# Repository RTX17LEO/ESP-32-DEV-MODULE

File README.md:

ESP32 Dev Board Project

The ESP32 Dev Module is a powerful microcontroller with built-in Wi-Fi and Bluetooth, widely used for IoT and embedded applications.  
This project includes the schematic and PCB design of an ESP32 Dev Module created using KiCad.  
The schematic defines connections for power, EN pin, and basic components like resistors and capacitors.  
A 2-layer PCB is designed with proper routing and clearance rules followed.  
KiCad is used for schematic capture, footprint assignment, and PCB layout, and Gerber files are generated for manufacturing.

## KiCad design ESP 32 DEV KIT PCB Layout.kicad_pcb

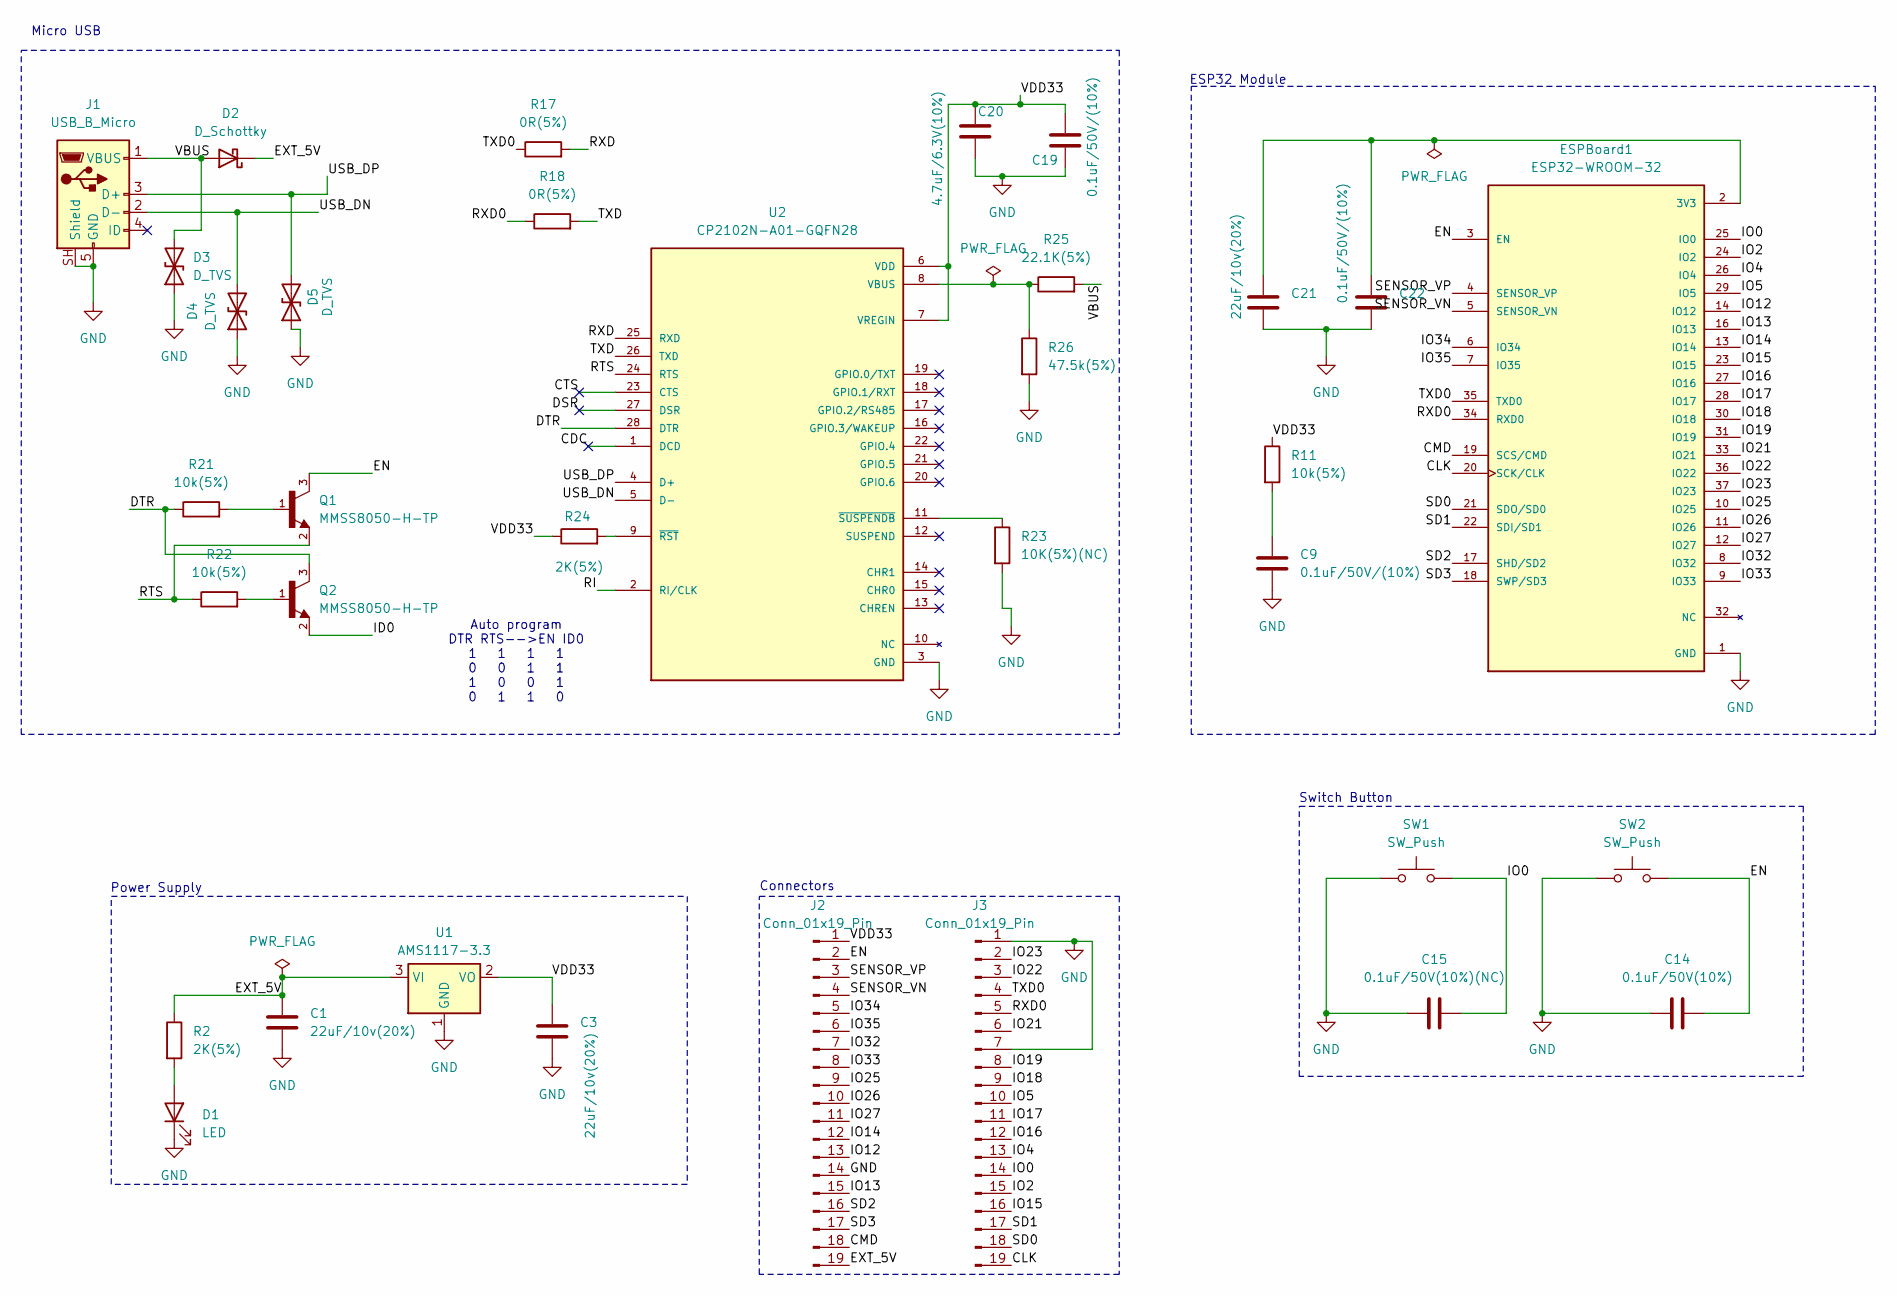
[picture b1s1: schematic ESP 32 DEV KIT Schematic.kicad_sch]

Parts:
C1, C3, C21: 22uF/10v(20%); C_0201_0603Metric
C9, C19, C22: 0.1uF/50V/(10%); C_01005_0402Metric
C14: 0.1uF/50V(10%); C_01005_0402Metric
C15: 0.1uF/50V(10%)(NC); C_01005_0402Metric
C20: 4.7uF/6.3V(10%); C_01005_0402Metric
D1: LED; LED_0603_1608Metric
D2: D_Schottky; D_SOD-323
D3, D4, D5: D_TVS; D_SOD-523
ESPBoard1: ESP32-WROOM-32; MODULE_ESP32-WROOM-32; PARTREV 2.9
J1: USB_B_Micro; USB_Micro-B_Molex_47346-0001
J2, J3: Conn_01x19_Pin; PinHeader_1x19_P2.54mm_Vertical
Q1, Q2: MMSS8050-H-TP; TRANS_MMSS8050-H-TP; PARTREV D
R2, R24: 2K(5%); R_01005_0402Metric
R11, R21, R22: 10k(5%); R_01005_0402Metric
R17, R18: 0R(5%); R_01005_0402Metric
R23: 10K(5%)(NC); R_01005_0402Metric
R25: 22.1K(5%); R_01005_0402Metric
R26: 47.5k(5%); R_01005_0402Metric
SW1, SW2: SW_Push; SW_SPST_B3S-1000
U1: AMS1117-3.3; SOT-223-3_TabPin2
U2: CP2102N-A01-GQFN28; QFN50P500X500X80-29N; PARTREV 1.0

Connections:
/CDC: U2.1 (DCD)
/CLK: ESPBoard1.20 (SCK/CLK), J3.19
/CMD: ESPBoard1.19 (SCS/CMD), J2.18
/CTS: U2.23 (CTS)
/DSR: U2.27 (DSR)
/DTR: Q2.3, R21.1, U2.28 (DTR)
/EN: C14.2, ESPBoard1.3 (EN), J2.2, Q1.3, SW2.2; also elsewhere on the board
/EXT_5V: C1.1, D2.1 (K), J2.19, R2.1, U1.3 (VI)
/ID0: Q2.2
/IO0: C15.2, ESPBoard1.25 (IO0), J3.14, SW1.2; also elsewhere on the board
/IO2: ESPBoard1.24 (IO2), J3.15
/IO4: ESPBoard1.26 (IO4), J3.13
/IO5: ESPBoard1.29 (IO5), J3.10
/IO12: ESPBoard1.14 (IO12), J2.13
/IO13: ESPBoard1.16 (IO13), J2.15
/IO14: ESPBoard1.13 (IO14), J2.12
/IO15: ESPBoard1.23 (IO15), J3.16
/IO16: ESPBoard1.27 (IO16), J3.12
/IO17: ESPBoard1.28 (IO17), J3.11
/IO18: ESPBoard1.30 (IO18), J3.9
/IO19: ESPBoard1.31 (IO19), J3.8
/IO21: ESPBoard1.33 (IO21), J3.6
/IO22: ESPBoard1.36 (IO22), J3.3
/IO23: ESPBoard1.37 (IO23), J3.2
/IO25: ESPBoard1.10 (IO25), J2.9
/IO26: ESPBoard1.11 (IO26), J2.10
/IO27: ESPBoard1.12 (IO27), J2.11
/IO32: ESPBoard1.8 (IO32), J2.7
/IO33: ESPBoard1.9 (IO33), J2.8
/IO34: ESPBoard1.6 (IO34), J2.5
/IO35: ESPBoard1.7 (IO35), J2.6
/RI: U2.2 (RI/CLK)
/RTS: Q1.2, R22.1, U2.24 (RTS)
/RXD: R17.2, U2.25 (RXD)
/RXD0: ESPBoard1.34 (RXD0), J3.5, R18.1
/SD0: ESPBoard1.21 (SDO/SD0), J3.18
/SD1: ESPBoard1.22 (SDI/SD1), J3.17
/SD2: ESPBoard1.17 (SHD/SD2), J2.16
/SD3: ESPBoard1.18 (SWP/SD3), J2.17
/SENSOR_VN: ESPBoard1.5 (SENSOR_VN), J2.4
/SENSOR_VP: ESPBoard1.4 (SENSOR_VP), J2.3
/TXD: R18.2, U2.26 (TXD)
/TXD0: ESPBoard1.35 (TXD0), J3.4, R17.1
/USB_DN: D4.2 (A2), J1.2 (D-), U2.5 (D-)
/USB_DP: D5.2 (A2), J1.3 (D+), U2.4 (D+)
/VBUS: D2.2 (A), D3.2 (A2), J1.1 (VBUS), R25.2
/VDD33: C3.1, C19.1, C20.1, J2.1, R11.1, R24.1, U1.2 (VO), U2.6 (VDD), U2.7 (VREGIN)
GND: C1.2, C3.2, C9.2, C14.1, C15.1, C19.2, C20.2, C21.2, C22.2, D1.1 (K), D3.1 (A1), D4.1 (A1), D5.1 (A1), ESPBoard1.1 (GND), ESPBoard1.15 (GND), ESPBoard1.38 (GND), ESPBoard1.39_1 (GND), ESPBoard1.39_2 (GND), ESPBoard1.39_3 (GND), ESPBoard1.39_4 (GND), ESPBoard1.39_5 (GND), ESPBoard1.39_6 (GND), ESPBoard1.39_7 (GND), ESPBoard1.39_8 (GND), ESPBoard1.39_9 (GND), ESPBoard1.39_10 (GND), ESPBoard1.39_11 (GND), ESPBoard1.39_12 (GND), ESPBoard1.39_13 (GND), ESPBoard1.39_14 (GND), ESPBoard1.39_15 (GND), ESPBoard1.39_16 (GND), ESPBoard1.39_17 (GND), ESPBoard1.39_18 (GND), ESPBoard1.39_19 (GND), ESPBoard1.39_20 (GND), ESPBoard1.39_21 (GND), J1.5 (GND), J1.SH (Shield), J2.14, J3.1, J3.7, R23.2, R26.2, SW1.1, SW2.1, U1.1 (GND), U2.3 (GND), U2.29 (GND); also elsewhere on the board
unnamed: C9.1, R11.2
unnamed: D1.2 (A), R2.2
unnamed: C21.1, C22.1, ESPBoard1.2 (3V3)
unnamed: Q1.1, R21.2
unnamed: Q2.1, R22.2
unnamed: R25.1, R26.1, U2.8 (VBUS)
unnamed: R24.2, U2.9 (~RST)
unnamed: R23.1, U2.11 (~SUSPENDB)

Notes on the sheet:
Micro USB
Auto program DTR RTS-->EN ID0 1 1 1 1 0 0 1 1 1 0 0 1 0 1 1 0
Power Supply
Switch Button
ESP32 Module
Connectors

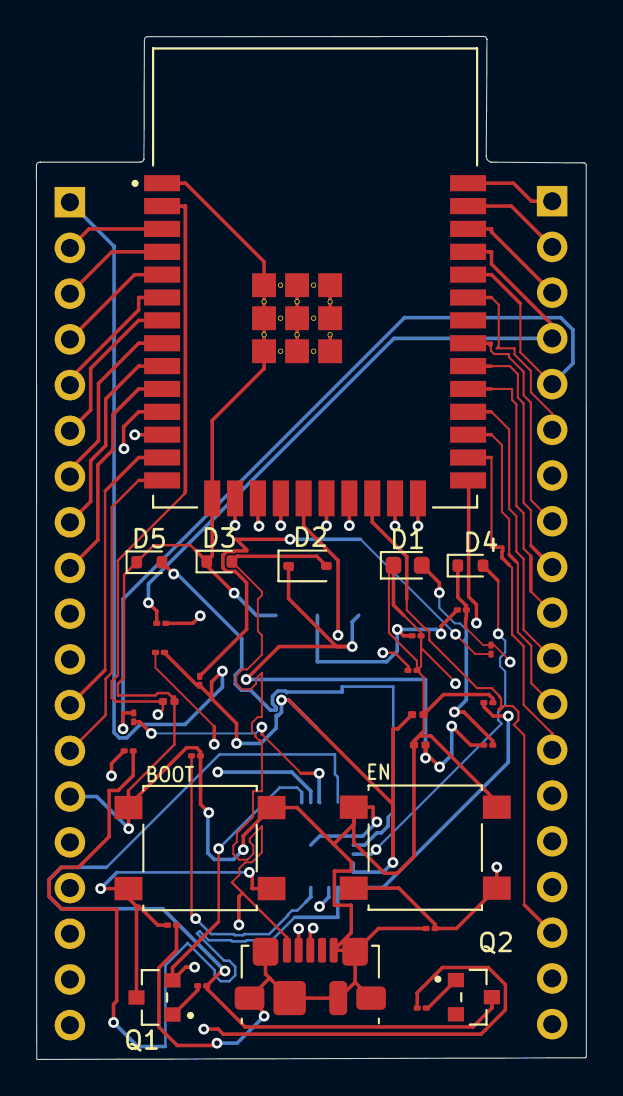
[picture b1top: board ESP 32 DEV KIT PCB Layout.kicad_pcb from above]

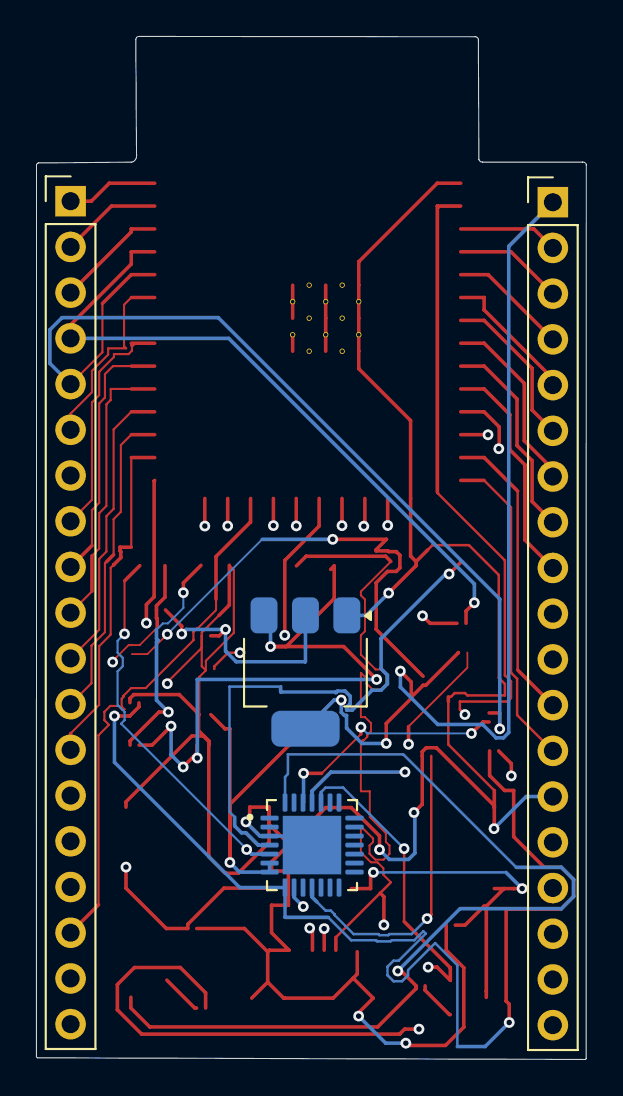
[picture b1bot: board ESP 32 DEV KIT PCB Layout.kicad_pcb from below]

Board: 4 copper layers, 30.5 x 56.8 mm, 34 parts (4 on the bottom side), 51 nets.

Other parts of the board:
BOOT: SW_Push; SW_SPST_B3S-1000
EN: SW_Push; SW_SPST_B3S-1000

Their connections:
/EN: BOOT.2; also elsewhere on the board
/IO0: EN.2; also elsewhere on the board
GND: BOOT.1, EN.1; also elsewhere on the board

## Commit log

2026-06-28 ESP 32 DEV Module
